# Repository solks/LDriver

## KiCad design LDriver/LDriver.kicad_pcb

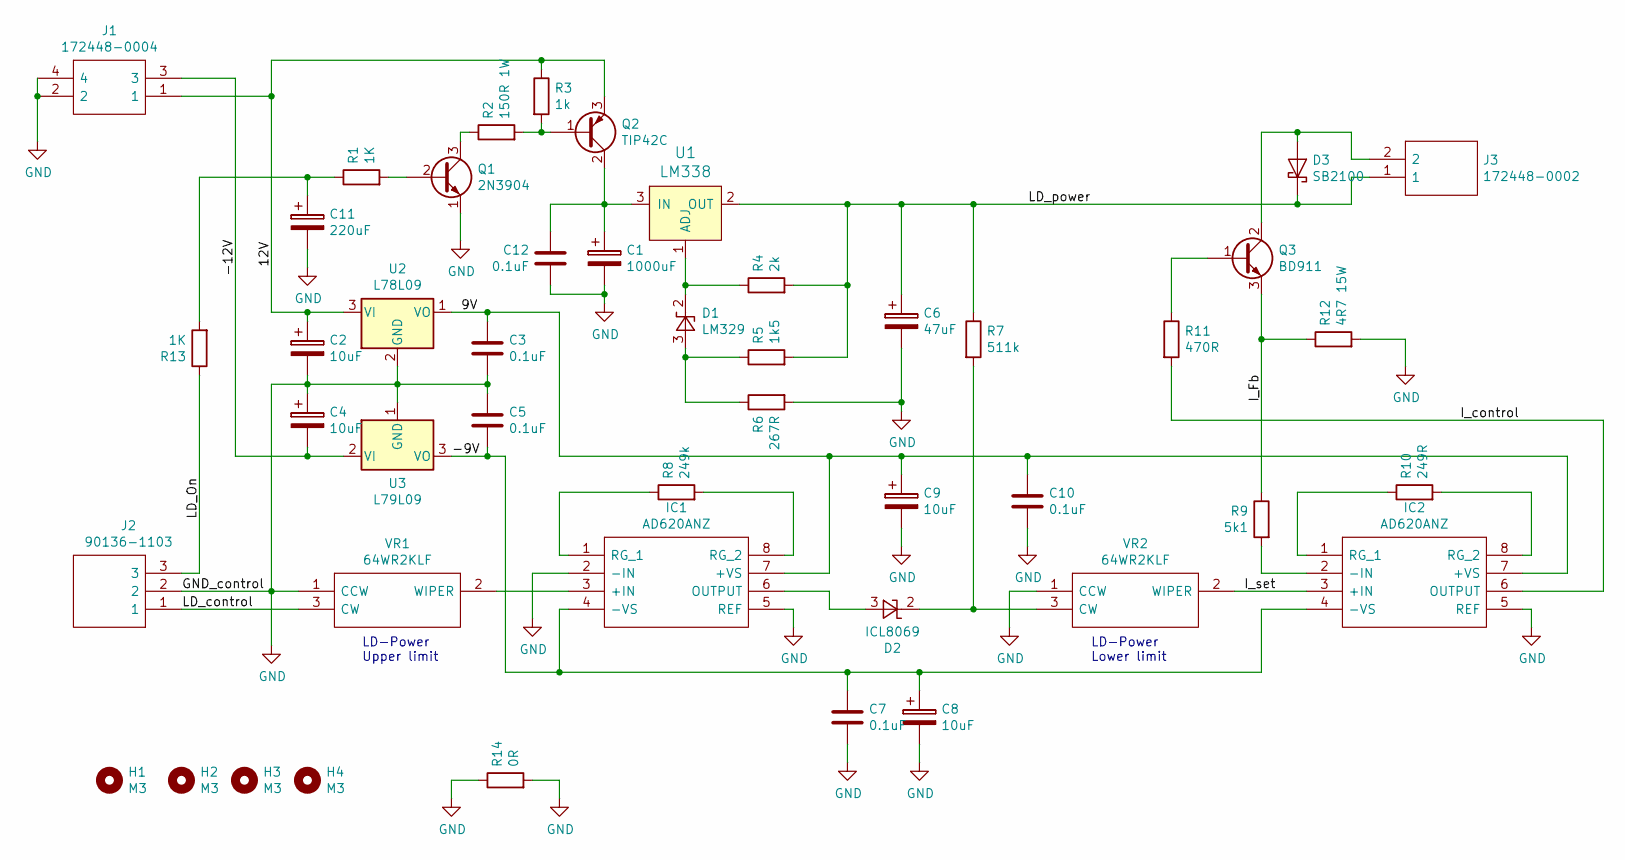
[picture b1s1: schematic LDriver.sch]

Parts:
C1: 1000uF; CP_Radial_D10.0mm_P5.00mm
C2, C4, C8, C9: 10uF; CP_Radial_D6.3mm_P2.50mm
C3, C5, C7, C10, C12: 0.1uF; C_Rect_L7.0mm_W4.5mm_P5.00mm
C6: 47uF; CP_Radial_D6.3mm_P2.50mm
C11: 220uF; CP_Radial_D6.3mm_P2.50mm
D1: LM329; TO-92_Inline
D2: ICL8069; TO-92_Inline
D3: SB2100; D_DO-15_P10.16mm_Horizontal
H1, H2, H3, H4: M3; MountingHole_3.2mm_M3
IC1, IC2: AD620ANZ; DIP794W56P254L959H533Q8N; Mouser Part Number 584-AD620ANZ
J1: 172448-0004; 1724480004; Mouser Part Number 538-172448-0004
J2: 90136-1103; SHDR3W65P0X254_1X3_1097X721X1110P; Mouser Part Number 538-90136-1103
J3: 172448-0002; 1724480002; Mouser Part Number 538-172448-0002
Q1: 2N3904; TO-92_Inline
Q2: TIP42C; TO-220-3_Vertical
Q3: BD911; TO-220-3_Vertical
R1, R13: 1K; R_Axial_DIN0207_L6.3mm_D2.5mm_P7.62mm_Horizontal
R2: 150R 1W; R_Axial_DIN0414_L11.9mm_D4.5mm_P15.24mm_Horizontal
R3: 1k; R_Axial_DIN0207_L6.3mm_D2.5mm_P7.62mm_Horizontal
R4: 2k; R_Axial_DIN0207_L6.3mm_D2.5mm_P10.16mm_Horizontal
R5: 1k5; R_Axial_DIN0207_L6.3mm_D2.5mm_P10.16mm_Horizontal
R6: 267R; R_Axial_DIN0207_L6.3mm_D2.5mm_P10.16mm_Horizontal
R7: 511k; R_Axial_DIN0207_L6.3mm_D2.5mm_P7.62mm_Horizontal
R8: 249k; R_Axial_DIN0207_L6.3mm_D2.5mm_P7.62mm_Horizontal
R9: 5k1; R_Axial_DIN0207_L6.3mm_D2.5mm_P7.62mm_Horizontal
R10: 249R; R_Axial_DIN0207_L6.3mm_D2.5mm_P10.16mm_Horizontal
R11: 470R; R_Axial_DIN0207_L6.3mm_D2.5mm_P10.16mm_Horizontal
R12: 4R7 15W; R_Axial_Power_L38.0mm_W9.0mm_P40.64mm
R14: 0R; R_2512_6332Metric_Pad1.52x3.35mm_HandSolder
U1: LM338; TO-220-3; MPN LM317T; Digi-Key_PN 497-1575-5-ND
U2: L78L09; TO-92_Inline
U3: L79L09; TO-92_Inline
VR1, VR2: 64WR2KLF; Mouser Part Number 858-64WR2KLF

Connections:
/9V: C3.1, C9.1, C10.1, IC1.7 (+VS), IC2.7 (+VS), U2.1 (VO)
/12V: C2.1, J1.1, Q2.3 (E), R3.1, U2.3 (VI)
/-9V: C5.2, C7.1, C8.1, IC1.4 (-VS), IC2.4 (-VS), U3.3 (VO)
/-12V: C4.2, J1.3, U3.2 (VI)
/I_Fb: Q3.3 (E), R9.1, R12.1
/I_control: IC2.6 (OUTPUT), R11.2
/I_set: IC2.3 (+IN), VR2.2 (WIPER)
/LD_On: J2.3, R13.1
/LD_control: J2.1, VR1.3 (CW)
/LD_power: C6.1, D3.1 (K), J3.1, R4.2, R5.2, R7.1, U1.2 (OUT)
GND: C1.2, C2.2, C3.2, C4.1, C5.1, C6.2, C7.2, C8.2, C9.2, C10.2, C11.2, C12.2, IC1.2 (-IN), IC1.5 (REF), IC2.5 (REF), J1.2, J1.4, J2.2, Q1.1 (E), R6.2, R12.2, R14.1, R14.2, U2.2 (GND), U3.1 (GND), VR1.1 (CCW), VR2.1 (CCW)
unnamed: C1.1, C12.1, Q2.2 (C), U1.3 (IN)
unnamed: C11.1, R1.1, R13.2
unnamed: D1.2 (K), R4.1, U1.1 (ADJ)
unnamed: D1.3 (A), R5.1, R6.1
unnamed: D2.2 (K), R7.2, VR2.3 (CW)
unnamed: D2.3 (A), IC1.6 (OUTPUT)
unnamed: D3.2 (A), J3.2, Q3.2 (C)
unnamed: IC1.1 (RG_1), R8.1
unnamed: IC1.3 (+IN), VR1.2 (WIPER)
unnamed: IC1.8 (RG_2), R8.2
unnamed: IC2.1 (RG_1), R10.1
unnamed: IC2.2 (-IN), R9.2
unnamed: IC2.8 (RG_2), R10.2
unnamed: Q1.2 (B), R1.2
unnamed: Q1.3 (C), R2.1
unnamed: Q2.1 (B), R2.2, R3.2
unnamed: Q3.1 (B), R11.1

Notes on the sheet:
LD-Power Upper limit
LD-Power Lower limit

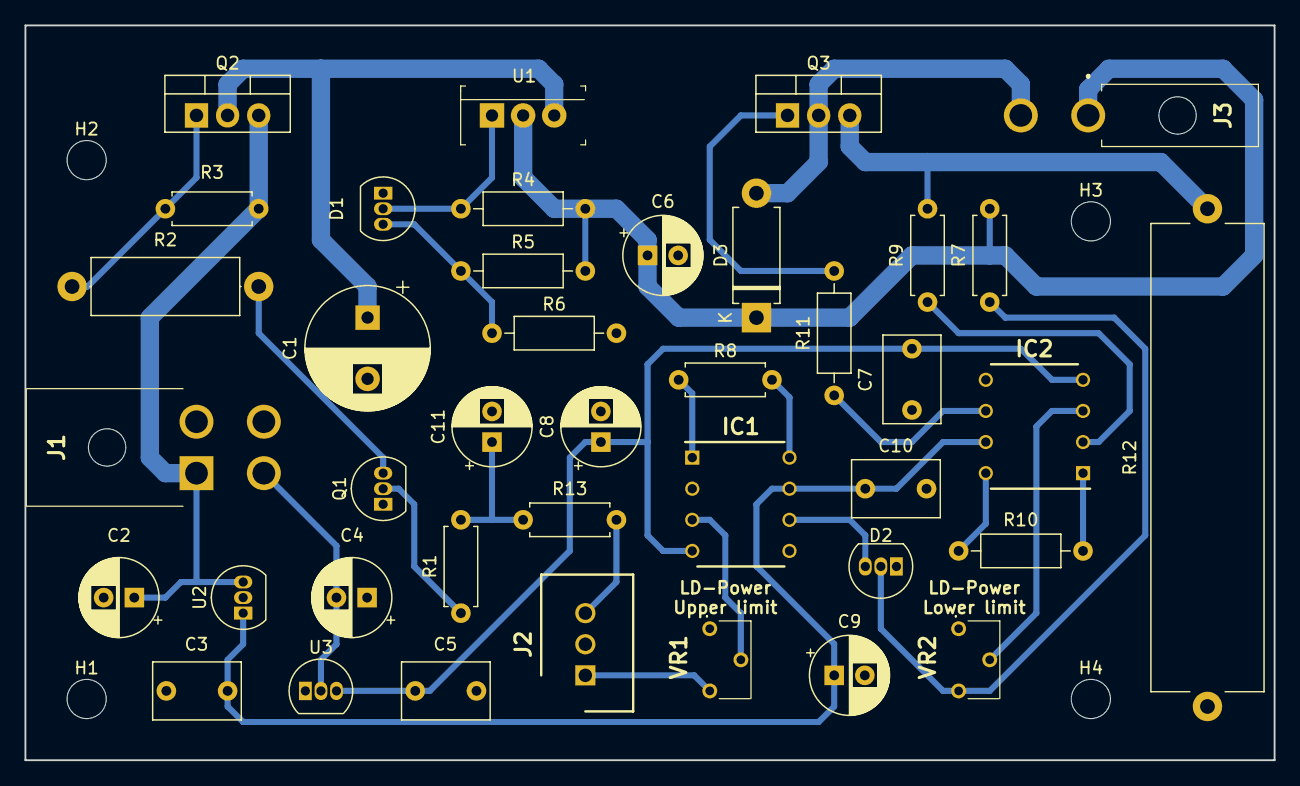
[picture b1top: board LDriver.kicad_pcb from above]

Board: 2 copper layers, 102.0 x 60.0 mm, 45 parts (1 on the bottom side), 28 nets.

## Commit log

2022-02-17 v1.0 LDD
